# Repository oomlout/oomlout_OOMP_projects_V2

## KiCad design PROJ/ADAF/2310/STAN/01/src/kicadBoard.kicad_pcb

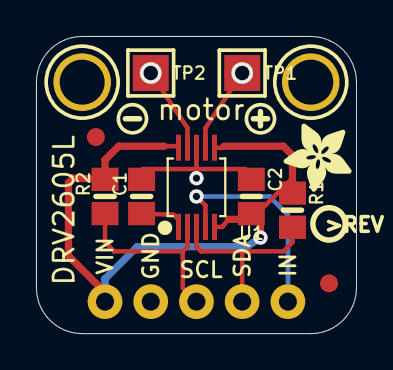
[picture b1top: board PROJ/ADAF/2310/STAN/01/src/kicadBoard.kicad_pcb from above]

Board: 2 copper layers, 17.8 x 16.5 mm, 16 parts (0 on the bottom side), 8 nets.

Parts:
C1, C2: 1uF; 0805-NO
FID1, FID2: FIDUCIAL""; FIDUCIAL_1MM
JP1: 1X05_ROUND_FULL_76
R1, R2: 10K; 0805-NO
TP1, TP2: TESTPOINT_PAD_2MM
U1: DRV2605LDGS; PSOP10
U$2, U$3: MOUNTINGHOLE2.5; MOUNTINGHOLE_2.5_PLATED
U$4: SYMBOL_PLUS
U$5: SYMBOL_MINUS
U$15: PCBFEAT-REV-040
U$18: ADAFRUIT_3.5MM

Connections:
GND: C1.1, C2.2, JP1.2, U1.8
IN/TRIG: JP1.5, U1.4
unnamed: C1.2, U1.1
OUT+: TP1.P$1, U1.7
OUT-: TP2.P$1, U1.9
SCL: JP1.3, R2.1, U1.2
SDA: JP1.4, R1.1, U1.3
VIN: C2.1, JP1.1, R1.2, R2.2, U1.5, U1.6, U1.10

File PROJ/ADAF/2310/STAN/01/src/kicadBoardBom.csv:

"Id";"Designator";"Package";"Quantity";"Designation";"Supplier and ref";
1;"R1,R2";"0805-NO";2;"10K";;;
2;"U$2,U$3";"MOUNTINGHOLE_2.5_PLATED";2;"MOUNTINGHOLE2.5";;;
3;"FID2,FID1";"FIDUCIAL_1MM";2;"FIDUCIAL""";;;
4;"U$18";"ADAFRUIT_3.5MM";1;"";;;
5;"TP2,TP1";"TESTPOINT_PAD_2MM";2;"";;;
6;"U$4";"SYMBOL_PLUS";1;"";;;
7;"JP1";"1X05_ROUND_FULL_76";1;"";;;
8;"U$5";"SYMBOL_MINUS";1;"";;;
9;"C1,C2";"0805-NO";2;"1uF";;;
10;"U$15";"PCBFEAT-REV-040";1;"";;;
11;"U1";"PSOP10";1;"DRV2605LDGS";;;

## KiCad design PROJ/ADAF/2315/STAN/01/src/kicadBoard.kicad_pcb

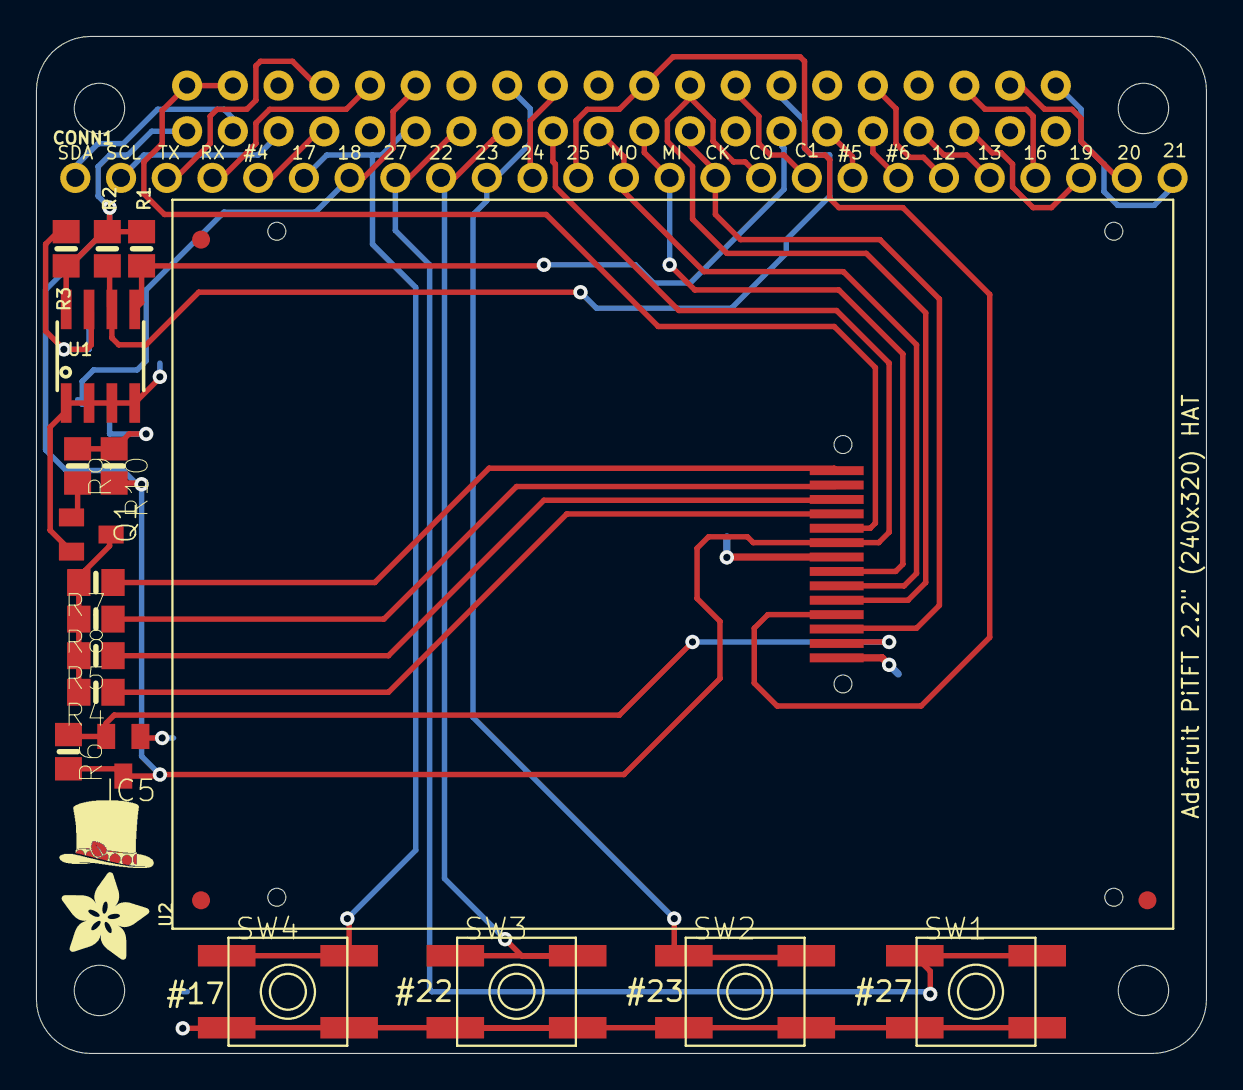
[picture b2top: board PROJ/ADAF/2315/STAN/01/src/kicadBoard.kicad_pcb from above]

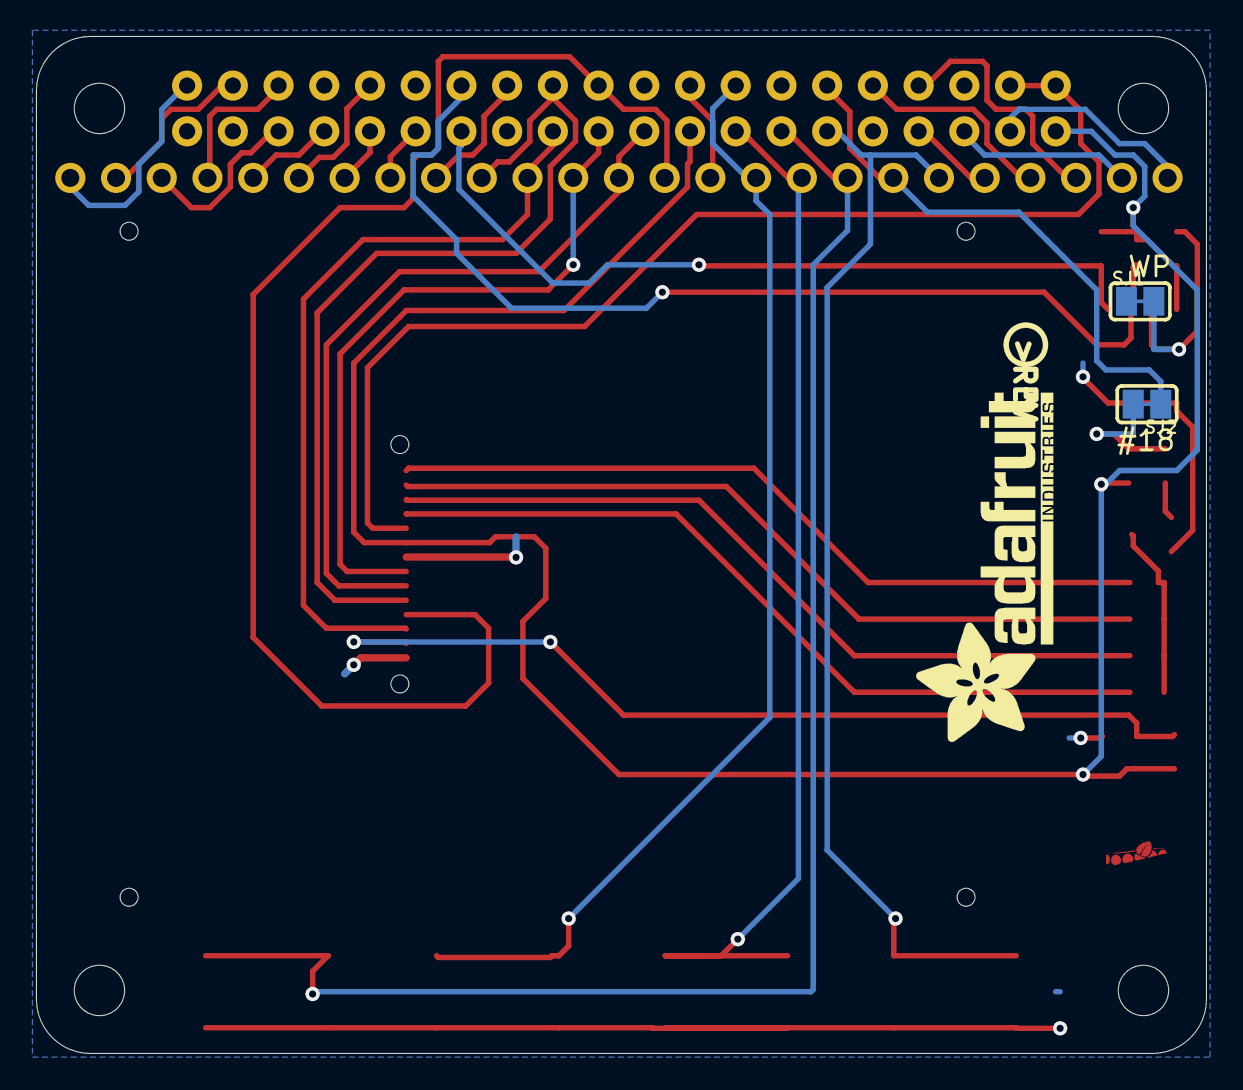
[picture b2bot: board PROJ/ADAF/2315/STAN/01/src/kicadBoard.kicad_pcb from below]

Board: 2 copper layers, 65.0 x 56.5 mm, 29 parts (4 on the bottom side), 39 nets.

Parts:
CONN1: HEADER-1X25; 1X25_ROUND_70MIL
FID1, FID2, FID3: FIDUCIAL""; FIDUCIAL_1MM
IC5: AXP803; SOT23
Q1: MMBT2222; SOT23-BEC
R1, R2, R3: 3.9K; 0805-NO
R4, R5, R7, R8: 100; 0805-NO
R6: 10K; 0805-NO
R9, R10: 1K; 0805-NO
RPI1: RASPBERRYPI_BPLUS_HATNOSLOTS; PI_HAT_NOSLOTS
SJ1: WP; SOLDERJUMPER_CLOSEDWIRE
SJ2: BACKLITE; SOLDERJUMPER_CLOSEDWIRE
SW1, SW2, SW3, SW4: SPST_TACT-EVQQ2; EVQ-Q2
U1: CAT24C32; SOIC8_150MIL
U2: 2.2TFT; TM022HDH26_2.2IN_LCD
U$1: ADAFRUIT_5MM
U$3: ADAFRUIT_TEXT_20MM
U$4: PIHATLOGO
U$12: PCBFEAT-REV-056

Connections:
3.3V: IC5.3, R1.2, R2.2, R3.2, R6.2, R10.2, RPI1.1, RPI1.17, U1.8, U2.9
5.0V: RPI1.2, RPI1.4, U2.10
EECLK: R2.1, RPI1.28, U1.6
EEDATA: R1.1, RPI1.27, U1.5
GND: IC5.1, Q1.E, RPI1.6, RPI1.9, RPI1.14, RPI1.20, RPI1.25, RPI1.30, RPI1.34, RPI1.39, SJ1.1, SW1.A, SW1.A', SW2.A, SW2.A', SW3.A, SW3.A', SW4.A, SW4.A', U1.1, U1.2, U1.3, U1.4, U2.1, U2.8
GPIO4: CONN1.5, RPI1.7
GPIO5: CONN1.18, RPI1.29
GPIO6: CONN1.19, RPI1.31
GPIO12: CONN1.20, RPI1.32
GPIO13: CONN1.21, RPI1.33
GPIO16: CONN1.22, RPI1.36
GPIO17: CONN1.6, RPI1.11, SW4.B, SW4.B'
GPIO18: CONN1.7, RPI1.12, SJ2.1
GPIO19: CONN1.23, RPI1.35
GPIO20: CONN1.24, RPI1.38
GPIO21: CONN1.25, RPI1.40
GPIO22: CONN1.9, RPI1.15, SW3.B, SW3.B'
GPIO23: CONN1.10, RPI1.16, SW2.B, SW2.B'
GPIO24: CONN1.11, RPI1.18
GPIO27: CONN1.8, RPI1.13, SW1.B, SW1.B'
unnamed: R4.1, U2.11
unnamed: R5.1, U2.12
unnamed: R7.1, U2.14
unnamed: R8.1, U2.13
unnamed: Q1.C, R4.2, R5.2, R7.2, R8.2
unnamed: Q1.B, R9.2
unnamed: R9.1, R10.1, SJ2.2
unnamed: R3.1, SJ1.2, U1.7
RXD: CONN1.4, RPI1.10
SCL: CONN1.2, RPI1.5
SDA: CONN1.1, RPI1.3
SPI_CE0: CONN1.16, RPI1.24, U2.5
SPI_CE1: CONN1.17, RPI1.26
SPI_MISO: CONN1.14, RPI1.21, U2.7
SPI_MOSI: CONN1.13, RPI1.19, U2.6
SPI_SCLK: CONN1.15, RPI1.23, U2.3
TFT_DC: CONN1.12, RPI1.22, U2.4
TFT_RST: IC5.2, R6.1, U2.2
TXD: CONN1.3, RPI1.8

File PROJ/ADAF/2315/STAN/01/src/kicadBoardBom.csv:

"Id";"Designator";"Package";"Quantity";"Designation";"Supplier and ref";
1;"SW2,SW3,SW1,SW4";"EVQ-Q2";4;"SPST_TACT-EVQQ2";;;
2;"FID1,FID3,FID2";"FIDUCIAL_1MM";3;"FIDUCIAL""";;;
3;"R10,R9";"0805-NO";2;"1K";;;
4;"IC5";"SOT23";1;"AXP803";;;
5;"Q1";"SOT23-BEC";1;"MMBT2222";;;
6;"U1";"SOIC8_150MIL";1;"CAT24C32";;;
7;"U2";"TM022HDH26_2.2IN_LCD";1;"2.2TFT";;;
8;"R8,R4,R5,R7";"0805-NO";4;"100";;;
9;"R6";"0805-NO";1;"10K";;;
10;"R2,R3,R1";"0805-NO";3;"3.9K";;;
11;"U$1";"ADAFRUIT_5MM";1;"";;;
12;"U$4";"PIHATLOGO";1;"";;;
13;"RPI1";"PI_HAT_NOSLOTS";1;"RASPBERRYPI_BPLUS_HATNOSLOTS";;;
14;"CONN1";"1X25_ROUND_70MIL";1;"HEADER-1X25";;;
15;"U$12";"PCBFEAT-REV-056";1;"";;;
16;"SJ1";"SOLDERJUMPER_CLOSEDWIRE";1;"WP";;;
17;"U$3";"ADAFRUIT_TEXT_20MM";1;"";;;
18;"SJ2";"SOLDERJUMPER_CLOSEDWIRE";1;"BACKLITE";;;

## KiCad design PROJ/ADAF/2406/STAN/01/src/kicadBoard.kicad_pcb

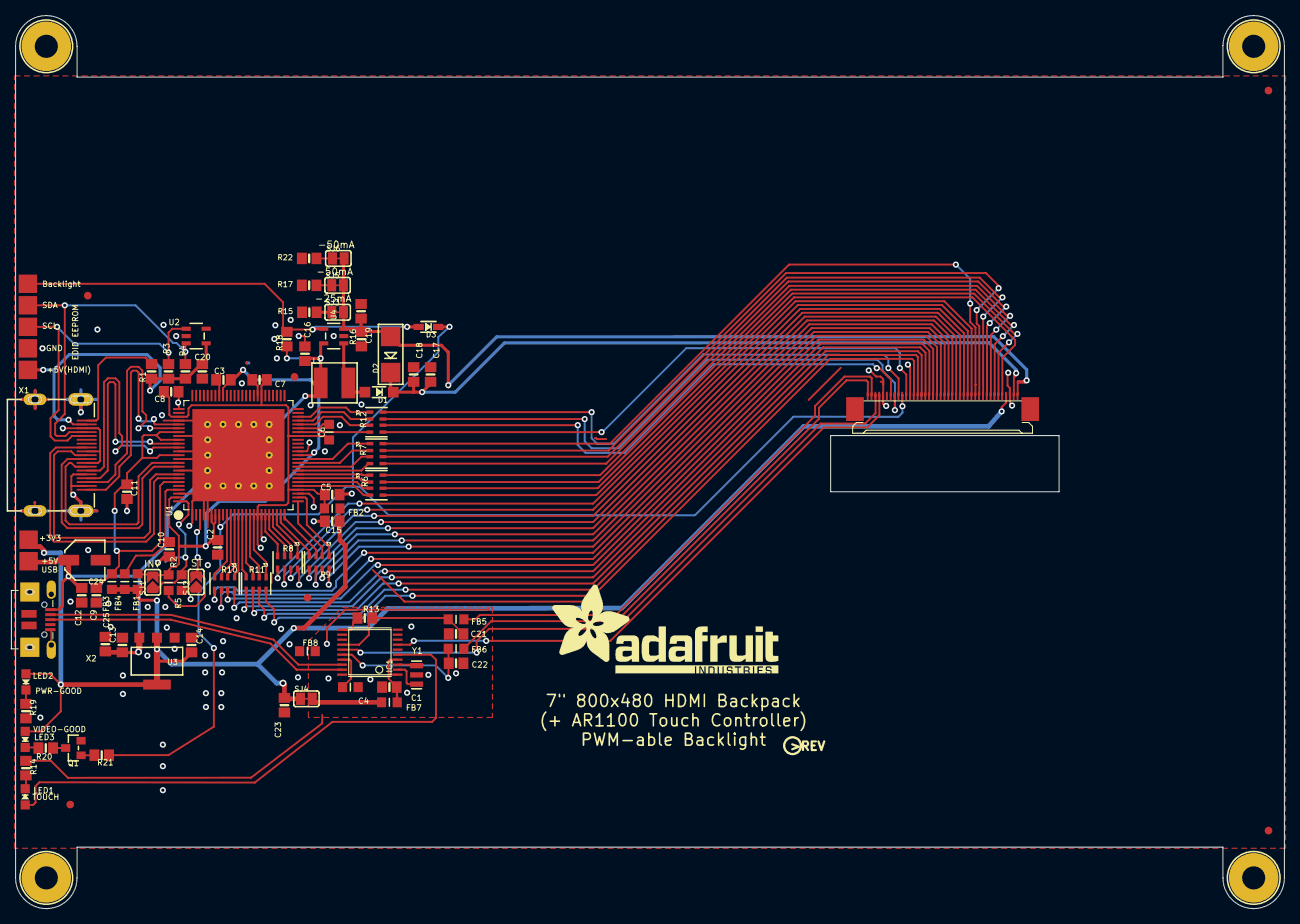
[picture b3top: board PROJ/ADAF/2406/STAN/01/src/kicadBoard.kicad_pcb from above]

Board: 2 copper layers, 165.1 x 116.2 mm, 97 parts (1 on the bottom side), 106 nets.

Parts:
BACKLITEPWM0: 1X01_SMD_MASKHELD_2X2MM
C1, C2, C3, C7, C8, C9, C10, C11, C19, C20, C23: 0.1uF; 0805-NO
C4, C6: 0.1uF; _0805MP
C5: 0.1u; 0805-NO
C12, C13, C14, C15, C16: 10uF; 0805-NO
C17, C18, C25: 1uF; 0805-NO
C21, C22: 0.01uF; 0805-NO
C24: 100uF/6V; PANASONIC_C
D1: MBR0540; SOD-123
D2: MM3Z24VT1G; SMADIODE
D3: 1N4148; SOD-323
FB1, FB2, FB3, FB4, FB5, FB6, FB7, FB8: Ferrite; _0805MP
FID1, FID2, FID3, FID4, FID5, FID6: FIDUCIAL""; FIDUCIAL_1MM
GND0: 1X01_SMD_MASKHELD_2X2MM
IC1: AR1100; TSSOP20-5.3MMBODY
J1: TFTLCD-40PIN-TTL-KD070; TFTLCD-KD070GD21-40NT
JP3, JP4, JP5, JP6, JP7: 1X01_SMD_MASKHELD_2X2MM
L1: 6.8uH; INDUCTOR_5X5MM_NR5040_NOTHERMALS
LED1: Red; CHIPLED_0805_NOOUTLINE
LED2: Green; CHIPLED_0805_NOOUTLINE
LED3: Blue; CHIPLED_0805_NOOUTLINE
Q1: BSS138; SOT23-WIDE
R1, R3, R4, R13, R18: 10K; 0805-NO
R2, R5: 10K; _0805MP
R6, R7, R8, R9, R10, R11, R12: 33; RESPACK_4X0603
R14, R19, R20, R21: 1K; 0805-NO
R15, R17: 6; 0805-NO
R16, R22: 12; 0805-NO
SJ1, SJ2: SOLDERJUMPER_ARROW_NOPASTE
SJ3, SJ5: -50mA; SOLDERJUMPER_CLOSEDWIRE
SJ4: SOLDERJUMPER_CLOSEDWIRE
SJ6: -25mA; SOLDERJUMPER_CLOSEDWIRE
U1: TFP401; S-PQFP-G100
U2: 24LC02BT-I/OT; SOT23-5
U3: LT1117(3V3); SOT223-R
U4: FAN5333BSX; SOT23-5
U$31, U$32, U$33, U$34: MOUNTINGHOLE3.0; MOUNTINGHOLE_3.0_PLATED
U$75: ADAFRUIT_TEXT_30MM
U$76: PCBFEAT-REV-056
X1: 47151-0001; HDMI_MOLEX_47151-0001_DIMLAYER
X2: MicroUSB; 4UCONN_20329
Y1: 12MHz; RESONATOR-SMD

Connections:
5.0V: C20.1, JP3.1, R1.2, R3.2, R4.2, U2.4, X1.18
24V: C17.1, C18.1, D1.C, D2.C, J1.2
ACTIVE: D3.C, J1.31, R21.1, U1.8
AGND: C1.1, C4.2, C21.2, C22.2, FB8.2, IC1.6, IC1.8, IC1.9, IC1.13, IC1.20, R14.2, Y1.2
ASD: R12.3, U1.46
AVDD: C9.1, C11.1, FB3.2, U1.82, U1.84, U1.88, U1.95
AVDD2: FB7.2, SJ4.2
B0: R10.4, U1.10
B1: R10.3, U1.11
B2: R10.2, U1.12
B3: R10.1, U1.13
B4: R11.4, U1.14
B5: R11.3, U1.15
B6: R11.2, U1.16
B7: R11.1, U1.17
CVB: R12.2, U1.47
D+: IC1.19, X2.D+
D-: IC1.18, X2.D-
DISPEN: J1.34, R12.6
G0: R8.4, U1.20
G1: R8.3, U1.21
G2: R8.2, U1.22
G3: R8.1, U1.23
G4: R9.4, U1.24
G5: R9.3, U1.25
G6: R9.2, U1.26
G7: R9.1, U1.27
GND: C2.2, C3.2, C5.2, C6.2, C7.2, C8.2, C9.2, C10.2, C11.2, C12.2, C13.2, C14.2, C15.2, C16.1, C17.2, C18.2, C19.2, C20.2, C23.2, C24.-, C25.2, FB8.1, GND0.1, J1.3, J1.29, J1.36, Q1.2, R5.1, R15.2, R16.2, R17.2, R19.2, R22.2, SJ2.1, U1.1, U1.4, U1.5, U1.19, U1.28, U1.39, U1.45, U1.58, U1.68, U1.76, U1.79, U1.83, U1.87, U1.89, U1.92, U1.98, U1.P$1, U1.P$2, U1.P$3, U1.P$4, U1.P$5, U1.P$6, U1.P$7, U1.P$8, U1.P$9, U1.P$10, U1.P$11, U1.P$12, U1.P$13, U1.P$14, U1.P$15, U1.P$16, U1.THERMAL, U2.2, U2.5, U3.1, U4.2, X1.2, X1.5, X1.8, X1.11, X1.17, X1.P$1, X1.P$2, X1.P$3, X1.P$4, X2.BASE@1, X2.BASE@2, X2.GND, X2.SPRT@1, X2.SPRT@2, X2.SPRT@3, X2.SPRT@4
HSYNC: J1.32, R12.8
LEDK: C19.1, D2.A, J1.1, R16.1, SJ3.2, SJ5.2, SJ6.2, U4.3
unnamed: U1.93, X1.10
unnamed: U1.94, X1.12
unnamed: U1.90, X1.7
unnamed: U1.91, X1.9
unnamed: U1.85, X1.4
unnamed: U1.86, X1.6
unnamed: U1.80, X1.1
unnamed: U1.81, X1.3
unnamed: R1.1, X1.19
unnamed: IC1.2, Y1.1
unnamed: IC1.3, Y1.3
unnamed: C4.1, IC1.17
unnamed: LED2.C, R19.1
unnamed: J1.5, R6.5
unnamed: J1.6, R6.6
unnamed: J1.7, R6.7
unnamed: J1.8, R6.8
unnamed: J1.9, R7.5
unnamed: J1.10, R7.6
unnamed: J1.11, R7.7
unnamed: J1.12, R7.8
unnamed: J1.13, R8.5
unnamed: J1.14, R8.6
unnamed: J1.15, R8.7
unnamed: J1.16, R8.8
unnamed: J1.17, R9.5
unnamed: J1.18, R9.6
unnamed: J1.19, R9.7
unnamed: J1.20, R9.8
unnamed: J1.21, R10.5
unnamed: J1.22, R10.6
unnamed: J1.23, R10.7
unnamed: J1.24, R10.8
unnamed: J1.25, R11.5
unnamed: J1.26, R11.6
unnamed: J1.27, R11.7
unnamed: R17.1, SJ5.1
unnamed: C10.1, FB4.2, U1.97
unnamed: J1.28, R11.8
unnamed: IC1.11, R13.2
unnamed: LED1.C, R14.1
unnamed: C5.1, C6.1, C7.1, C8.1, FB2.2, U1.18, U1.29, U1.43, U1.57, U1.78
unnamed: IC1.5, LED1.A
unnamed: R22.1, SJ6.1
unnamed: LED3.C, R20.1
unnamed: Q1.3, R20.2
unnamed: D1.A, L1.P$2, U4.1
unnamed: Q1.1, R21.2
unnamed: R15.1, SJ3.1
unnamed: BACKLITEPWM0.1, D3.A, R18.2, U4.4
unnamed: FB5.2, J1.39
unnamed: FB6.2, J1.40
unnamed: C1.2, FB7.1, IC1.1, IC1.4
OCK_INV: R5.2, SJ1.1, U1.100
PIXCLK: J1.30, R12.5
R0: R6.4, U1.30
R1: R6.3, U1.31
R2: R6.2, U1.32
R3: R6.1, U1.33
R4: R7.4, U1.34
R5: R7.3, U1.35
R6: R7.2, U1.36
R7: R7.1, U1.37
SCL: JP4.1, R3.1, U2.1, X1.15
SDA: JP5.1, R4.1, U2.3, X1.16
ST: R2.2, SJ2.2, U1.3
VDD: C14.1, C15.1, C23.1, FB1.1, FB2.1, FB3.1, FB4.1, J1.4, JP7.1, LED2.A, LED3.A, SJ4.1, U3.2, U3.4
VDDIO: C2.1, C3.1, FB1.2, R2.1, SJ1.2, U1.6, U1.7, U1.38, U1.67, U1.99
VIN: C12.1, C13.1, C16.2, C24.+, C25.1, JP6.1, L1.P$1, R18.1, U3.3, U4.5, X2.VBUS
VSYNC: J1.33, R12.7
X+: IC1.7, J1.37
X-: C21.1, FB5.1, IC1.14, R13.1
XCV: R12.1, U1.48
Y+: IC1.15, J1.38
Y-: C22.1, FB6.1, IC1.16
ZXC: R12.4, U1.44

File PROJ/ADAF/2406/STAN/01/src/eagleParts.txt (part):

Partlist

Exported from boardEagle.brd at 07/08/2022 17:31

EAGLE Version 9.6.2 Copyright (c) 1988-2020 Autodesk, Inc.

Assembly variant: 

Part        Value                  Package                          Library      Position (inch)       Orientation

BACKLITEPWM                        1X01_SMD_MASKHELD_2X2MM          microbuilder (0.06296063 3.20082677) R0
C1          0.1uF                  0805-NO                          microbuilder (1.9149685 1.13472441) R0
C2          0.1uF                  0805-NO                          microbuilder (1.03540157 1.85043307) R270
C3          0.1uF                  0805-NO                          microbuilder (1.06492913 2.70870079) R180
C4          0.1uF                  _0805MP                          microbuilder (1.7149685 1.13472441) R0
C5          0.1u                   0805-NO                          microbuilder (1.62201575 2.12102362) R0
C6          0.1uF                  _0805MP                          microbuilder (1.60626772 2.44098425) R90
C7          0.1uF                  0805-NO                          microbuilder (1.2499685 2.70870079) R180
C8          0.1uF                  0805-NO                          microbuilder (0.7972126 2.64767717) R0
C9          0.1uF                  0805-NO                          microbuilder (0.41370866 1.60523622) R270
C10         0.1uF                  0805-NO                          microbuilder (0.78737008 1.84059055) R270
C11         0.1uF                  0805-NO                          microbuilder (0.57083465 2.13586614) R270
C12         10uF                   0805-NO                          microbuilder (0.33890551 1.60523622) R270
C13         10uF                   0805-NO                          microbuilder (0.5472126 1.35043307) R90
C14         10uF                   0805-NO                          microbuilder (0.90154331 1.35043307) R90
C15         10uF                   0805-NO                          microbuilder (1.62201575 1.98429134) R180
C16         10uF                   0805-NO                          microbuilder (1.48225197 2.84255906) R270
C17         1uF                    0805-NO                          microbuilder (2.12595276 2.73625984) R90
C18         1uF                    0805-NO                          microbuilder (2.03933858 2.73625984) R90
C19         0.1uF                  0805-NO                          microbuilder (1.77162205 2.9173622) R270
C20         0.1uF                  0805-NO                          microbuilder (0.95666142 2.75200787) R270
C21         0.01uF                 0805-NO                          microbuilder (2.25646457 1.40692913) R180
C22         0.01uF                 0805-NO                          microbuilder (2.25646457 1.25692913) R0
C23         0.1uF                  0805-NO                          microbuilder (1.37725197 1.04228346) R270
C24         100uF/6V               PANASONIC_C                      microbuilder (0.3549685 1.785)     R180
C25         1uF                    0805-NO                          microbuilder (0.4599685 1.355)     R90
D1          MBR0540                SOD-123                          microbuilder (1.86217323 2.64570866) R180
D2          MM3Z24VT1G             SMADIODE                         microbuilder (1.92122835 2.83862205) R90
D3          1N4148                 SOD-323                          microbuilder (2.1149685 2.98)      R180
FB1         Ferrite                _0805MP                          microbuilder (0.62524409 1.67523622) R90
FB2         Ferrite                _0805MP                          microbuilder (1.62201575 2.05015748) R180
FB3         Ferrite                _0805MP                          microbuilder (0.49351181 1.67523622) R90
FB4         Ferrite                _0805MP                          microbuilder (0.55937795 1.67523622) R90
FB5         Ferrite                _0805MP                          microbuilder (2.25646457 1.48192913) R0
FB6         Ferrite                _0805MP                          microbuilder (2.25646457 1.33192913) R0
FB7         Ferrite                _0805MP                          microbuilder (1.9149685 1.05685039) R180
FB8         Ferrite                _0805MP                          microbuilder (1.4949685 1.31866142) R0
FID1        FIDUCIAL""             FIDUCIAL_1MM                     microbuilder (1.42910236 2.72444882) R0
FID2        FIDUCIAL""             FIDUCIAL_1MM                     microbuilder (1.49524409 1.59255906) R0
FID3        FIDUCIAL""             FIDUCIAL_1MM                     microbuilder (6.41847244 0.39980315) R0
FID4        FIDUCIAL""             FIDUCIAL_1MM                     microbuilder (0.3699685 3.14)      R0
FID5        FIDUCIAL""             FIDUCIAL_1MM                     microbuilder (0.2799685 0.53322835) R0
FID6        FIDUCIAL""             FIDUCIAL_1MM                     microbuilder (6.418 4.19062992)    R0
GND                                1X01_SMD_MASKHELD_2X2MM          microbuilder (0.06296063 2.87011811) R0
IC1         AR1100                 TSSOP20-5.3MMBODY                microbuilder (1.8149685 1.31366142) R90
J1          TFTLCD-40PIN-TTL-KD070 TFTLCD-KD070GD21-40NT            microbuilder (6.4999685 0.315)     MR0
JP3                                1X01_SMD_MASKHELD_2X2MM          microbuilder (0.06296063 2.75988189) R0
JP4                                1X01_SMD_MASKHELD_2X2MM          microbuilder (0.06296063 2.98035433) R0
JP5                                1X01_SMD_MASKHELD_2X2MM          microbuilder (0.06296063 3.09059055) R0
JP6                                1X01_SMD_MASKHELD_2X2MM          microbuilder (0.06689764 1.77956693) R0
JP7                                1X01_SMD_MASKHELD_2X2MM          microbuilder (0.06689764 1.88980315) R0
L1          6.8uH                  INDUCTOR_5X5MM_NR5040_NOTHERMALS microbuilder (1.63382677 2.69295276) R0
LED1        Red                    CHIPLED_0805_NOOUTLINE           microbuilder (0.04933858 0.57267717) R0
LED2        Green                  CHIPLED_0805_NOOUTLINE           microbuilder (0.05327559 1.16145669) R180
LED3        Blue                   CHIPLED_0805_NOOUTLINE           microbuilder (0.04933858 0.86706693) R180
Q1          BSS138                 SOT23-WIDE                       microbuilder (0.29611024 0.82279528) R90
R1          10K                    0805-NO                          microbuilder (0.6968189 2.75200787) R270
R2          10K                    _0805MP                          microbuilder (0.78402362 1.66976378) R270
R3          10K                    0805-NO                          microbuilder (0.78343307 2.75200787) R270
R4          10K                    0805-NO                          microbuilder (0.87004724 2.75200787) R270
R5          10K                    _0805MP                          microbuilder (0.85111024 1.67023622) R90
R6          33                     RESPACK_4X0603                   microbuilder (1.8483937 2.16933071) R270
R7          33                     RESPACK_4X0603                   microbuilder (1.8483937 2.33074803) R270
R8          33                     RESPACK_4X0603                   microbuilder (1.39366929 1.77366142) R180
R9          33                     RESPACK_4X0603                   microbuilder (1.55508661 1.77366142) R180
R10         33                     RESPACK_4X0603                   microbuilder (1.07083465 1.6653937) R180
R11         33                     RESPACK_4X0603                   microbuilder (1.23225197 1.6653937) R180
R12         33                     RESPACK_4X0603                   microbuilder (1.8483937 2.49216535) R270
R13         10K                    0805-NO                          microbuilder (1.78898425 1.48866142) R180
R14         1K                     0805-NO                          microbuilder (0.05311811 0.71980315) R90
R15         6                      0805-NO                          microbuilder (1.5049685 3.055)     R180
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
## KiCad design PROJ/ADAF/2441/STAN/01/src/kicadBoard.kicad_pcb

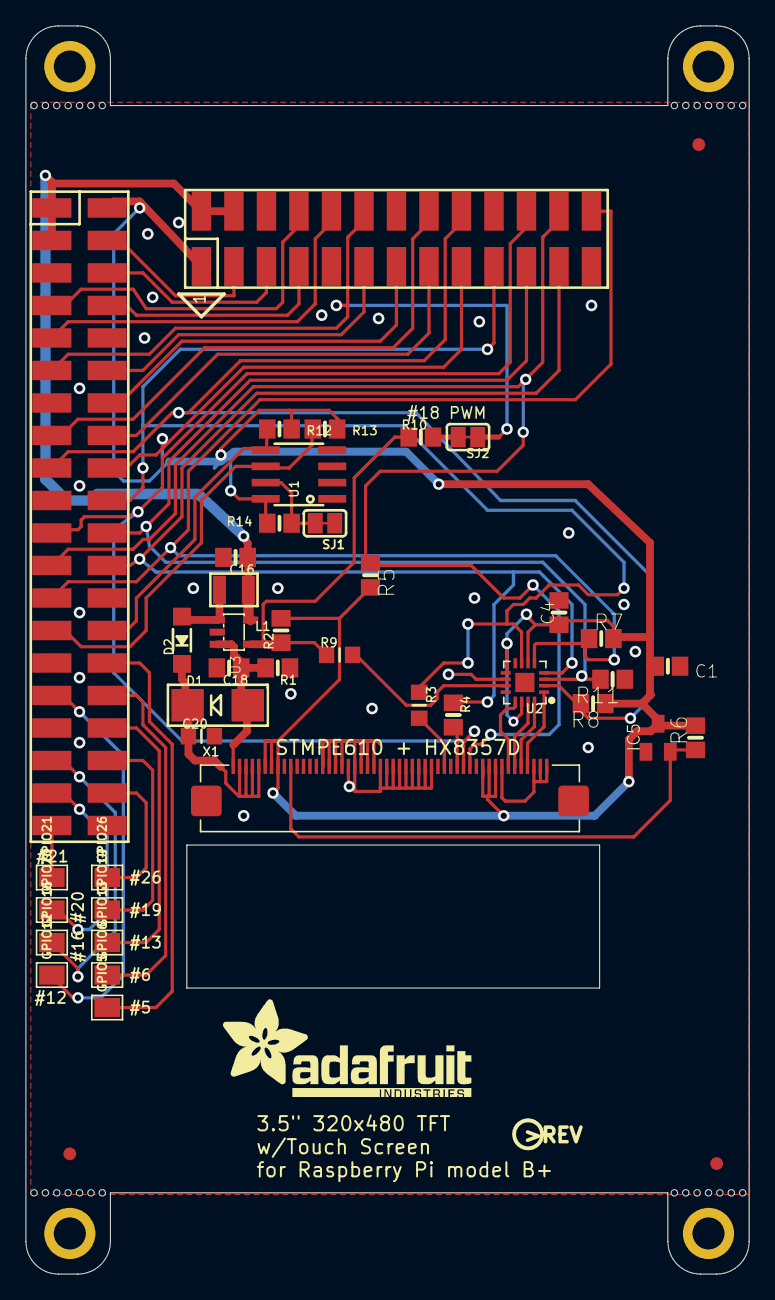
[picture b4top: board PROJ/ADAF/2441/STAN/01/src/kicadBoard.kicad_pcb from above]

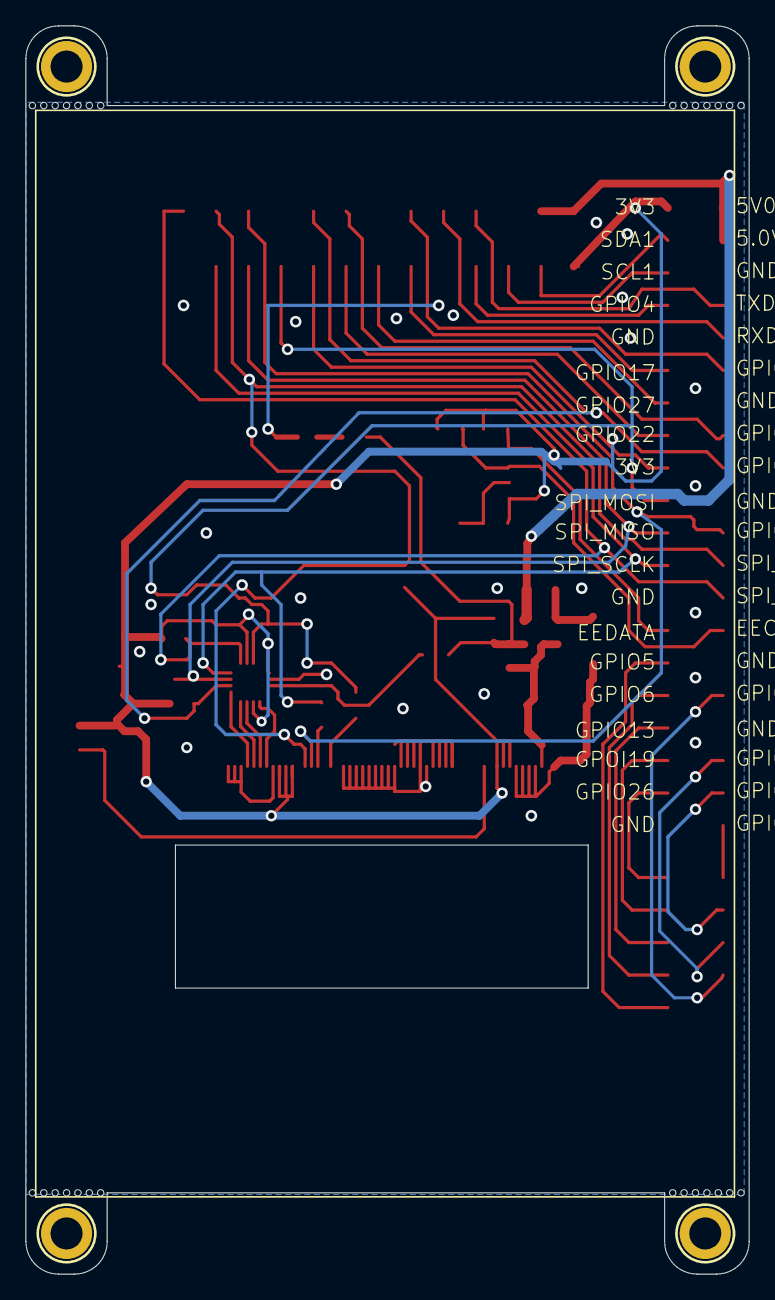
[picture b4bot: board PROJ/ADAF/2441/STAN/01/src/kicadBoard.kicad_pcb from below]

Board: 16 copper layers, 56.5 x 97.5 mm, 77 parts (6 on the bottom side), 45 nets.

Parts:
@HOLE0, @HOLE1, @HOLE2, @HOLE3, @HOLE4, @HOLE5, @HOLE6, @HOLE7, @HOLE8, @HOLE9, @HOLE10, @HOLE11, @HOLE12, @HOLE13, @HOLE14, @HOLE15, @HOLE16, @HOLE17, @HOLE18, @HOLE19, @HOLE20, @HOLE21, @HOLE22, @HOLE23, @HOLE24, @HOLE25, @HOLE26, @HOLE27: (no value)
C1, C16: 10uF; 0805-NO
C4, C18: 0.1uF; 0805-NO
C20: 1uF; _0805MP
D1: MM3Z24VT1G; SMADIODE
D2: MBR0540; SOD-123
GPIO5, GPIO6, GPIO12, GPIO13, GPIO16, GPIO19, GPIO20, GPIO21, GPIO26: PAD-1.5X2.0
IC5: AXP803; SOT23
JP1: 2X13_SMT_MALE
L1: 10uH 1007; INDUCTOR_1007
R1: 12Ω; 0805-NO
R2, R5, R6, R7, R11: 10K; 0805-NO
R3: 12; _0805MP
R4: 12; 0805-NO
R8: DNP; 0805-NO
R9: 1K; _0805MP
R10: 1K; 0805-NO
R12, R13, R14: 3.9K; 0805-NO
RPI1: RASPBERRYPI_BPLUS_SMT; RASPBERRYPI_BPLUS_SHIELD_SMT
SJ1: WP; SOLDERJUMPER_CLOSEDWIRE
SJ2: SOLDERJUMPER_CLOSEDWIRE
U1: CAT24C32; SOIC8_150MIL
U2: STMPE610; QFN16_3MM
U3: FAN5333BSX; SOT23-5@1
U$10, U$11, U$18: FIDUCIAL""; FIDUCIAL_1MM
U$15, U$16, U$17, U$20: MOUNTINGHOLE2.5_THICK; MOUNTINGHOLE_2.5_PLATED_THICK
U$19: PCBFEAT-REV-056
U$23: ADAFRUIT_TEXT_20MM
X1: TFT_3.5IN_320X480_50PIN

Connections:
3.3V: C1.1, C4.1, IC5.3, JP1.1, JP1.17, R2.2, R5.2, R6.2, R7.2, R8.1, R12.2, R13.2, R14.2, RPI1.1, RPI1.17, U1.8, U2.6, U2.9, U2.14, X1.6, X1.7, X1.8, X1.40, X1.41, X1.42
+5V: C16.1, JP1.2, JP1.4, L1.P$1, RPI1.2, RPI1.4, U3.5
+24V: C20.1, D1.C, D2.C, X1.2, X1.3, X1.4, X1.5
EECLK: R13.1, RPI1.28, U1.6
EEDATA: R12.1, RPI1.27, U1.5
GND: C1.2, C4.2, C16.2, C18.2, C20.2, IC5.1, JP1.6, JP1.9, JP1.14, JP1.20, JP1.25, R1.1, R11.1, RPI1.6, RPI1.9, RPI1.14, RPI1.20, RPI1.25, RPI1.30, RPI1.34, RPI1.39, SJ1.1, U1.1, U1.2, U1.3, U1.4, U2.10, U3.2, X1.15, X1.16, X1.17, X1.18, X1.19, X1.20, X1.21, X1.22, X1.23, X1.24, X1.25, X1.26, X1.27, X1.28, X1.29, X1.30, X1.31, X1.32, X1.43, X1.48, X1.49, X1.50
GPIO6: GPIO6.P$1, RPI1.31
GPIO16: GPIO16.P$1, RPI1.36
GPIO18: JP1.12, RPI1.12, SJ2.1
GPIO22: JP1.15, RPI1.15
GPIO23: JP1.16, RPI1.16
GPIO27: JP1.13, RPI1.13
LCD_LITE: R2.1, R9.1, R10.1, U3.4
LEDK: C18.1, D1.A, R1.2, U3.3, X1.1
MISO: JP1.21, R11.2, RPI1.21, U2.3
MOSI: JP1.19, R3.1, RPI1.19, U2.7
unnamed: R4.2, X1.36
unnamed: R3.2, X1.34
unnamed: R9.2, U2.11
unnamed: R10.2, SJ2.2
unnamed: GPIO5.P$1, RPI1.29
unnamed: JP1.3, RPI1.3
unnamed: JP1.5, RPI1.5
unnamed: JP1.7, RPI1.7
unnamed: GPIO13.P$1, RPI1.33
unnamed: GPIO19.P$1, RPI1.35
unnamed: JP1.11, RPI1.11
unnamed: D2.A, L1.P$2, U3.1
unnamed: GPIO26.P$1, RPI1.37
unnamed: GPIO12.P$1, RPI1.32
unnamed: GPIO20.P$1, RPI1.38
unnamed: R14.1, SJ1.2, U1.7
unnamed: JP1.10, RPI1.10
unnamed: JP1.8, RPI1.8
unnamed: GPIO21.P$1, RPI1.40
RT_CS: JP1.26, R7.1, RPI1.26, U2.5
RT_INT: JP1.18, R8.2, RPI1.18, U2.2
SCLK: JP1.23, R4.1, RPI1.23, U2.4
TFT_CS: JP1.24, R5.1, RPI1.24, X1.38
TFT_DC: JP1.22, RPI1.22, X1.37
TFT_RST: IC5.2, R6.1, X1.10
XL: U2.16, X1.46
XR: U2.13, X1.44
YD: U2.15, X1.45
YU: U2.1, X1.47

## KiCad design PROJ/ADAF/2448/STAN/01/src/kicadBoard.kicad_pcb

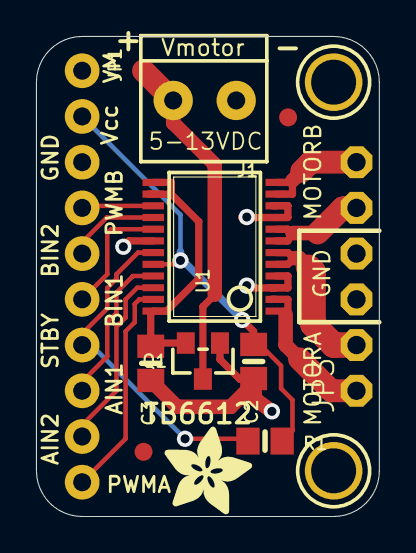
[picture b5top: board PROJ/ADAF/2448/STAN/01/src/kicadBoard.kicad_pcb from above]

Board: 2 copper layers, 19.1 x 26.7 mm, 14 parts (1 on the bottom side), 15 nets.

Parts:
C2, C3: 10µF; 0805-NO
FID1, FID2: FIDUCIAL""; FIDUCIAL_1MM
J1: VMOTORIN; TERMBLOCK_1X2-3.5MM
JP1: 1X10_ROUND_76
JP3: 1X06-CLEANBIG
Q1: DMG3415; SOT23-WIDE
R1: 10K; 0805-NO
U1: TB6612 SSOP; SSOP24
U$11: ADAFRUIT_3.5MM
U$13, U$14: MOUNTINGHOLE2.5; MOUNTINGHOLE_2.5_PLATED
U$15: ADAFRUIT_5MM

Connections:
AIN1: JP1.8, U1.21
AIN2: JP1.9, U1.22
BIN1: JP1.6, U1.17
BIN2: JP1.5, U1.16
GND: C2.2, C3.2, J1.2, JP1.3, JP3.3, JP3.4, Q1.1, U1.3, U1.4, U1.9, U1.10, U1.18
MA1: JP3.1, U1.1, U1.2
MA2: JP3.2, U1.5, U1.6
MB1: JP3.6, U1.11, U1.12
MB2: JP3.5, U1.7, U1.8
PWMA: JP1.10, U1.23
PWMB: JP1.4, U1.15
PWRIN: J1.1, JP1.1, Q1.3
STBY: JP1.7, R1.1, U1.19
VCC: C2.1, JP1.2, R1.2, U1.20
VMOTOR: C3.1, Q1.2, U1.13, U1.14, U1.24
